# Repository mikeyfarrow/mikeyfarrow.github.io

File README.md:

# mikeyfarrow.github.io
Github pages homepage

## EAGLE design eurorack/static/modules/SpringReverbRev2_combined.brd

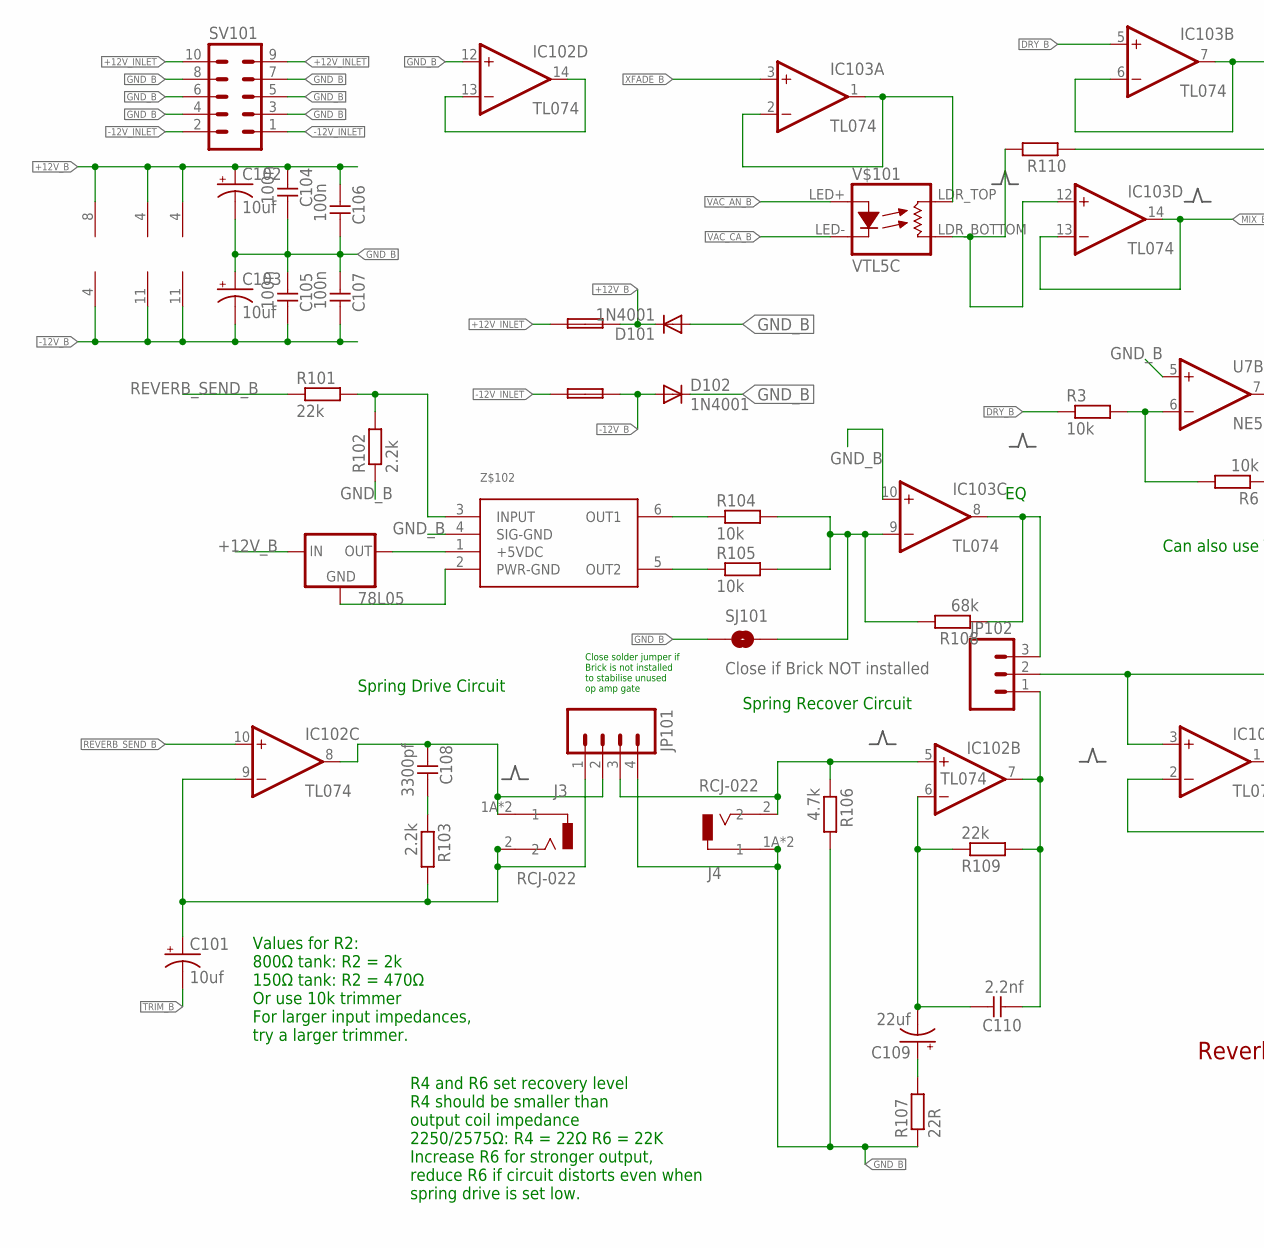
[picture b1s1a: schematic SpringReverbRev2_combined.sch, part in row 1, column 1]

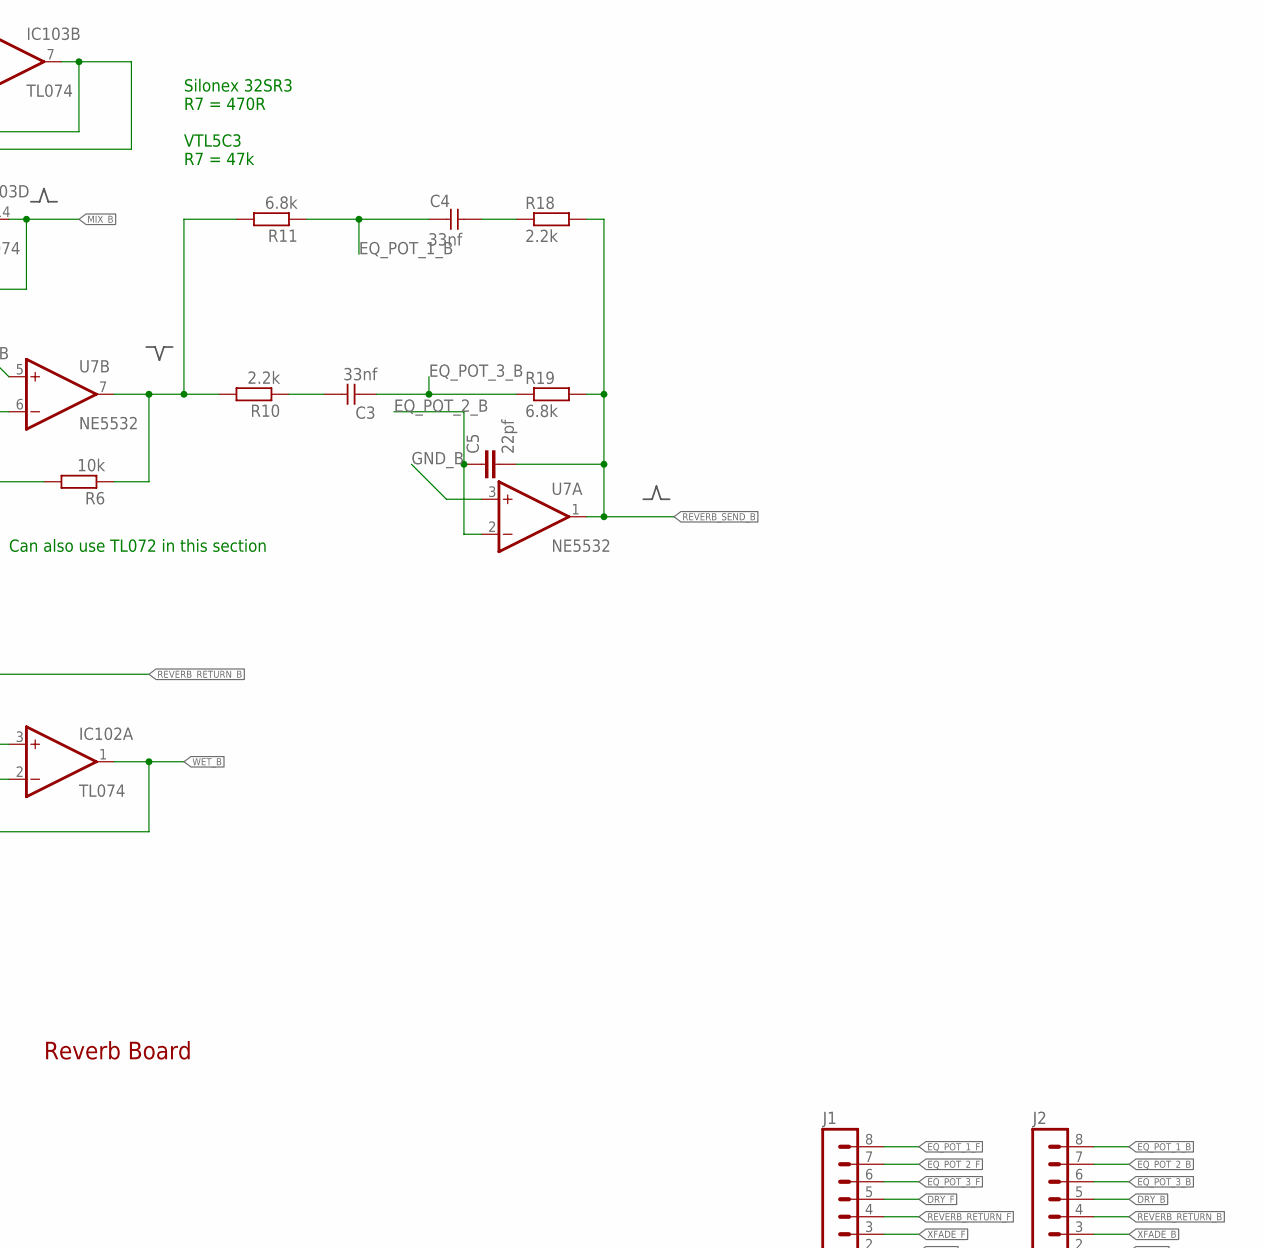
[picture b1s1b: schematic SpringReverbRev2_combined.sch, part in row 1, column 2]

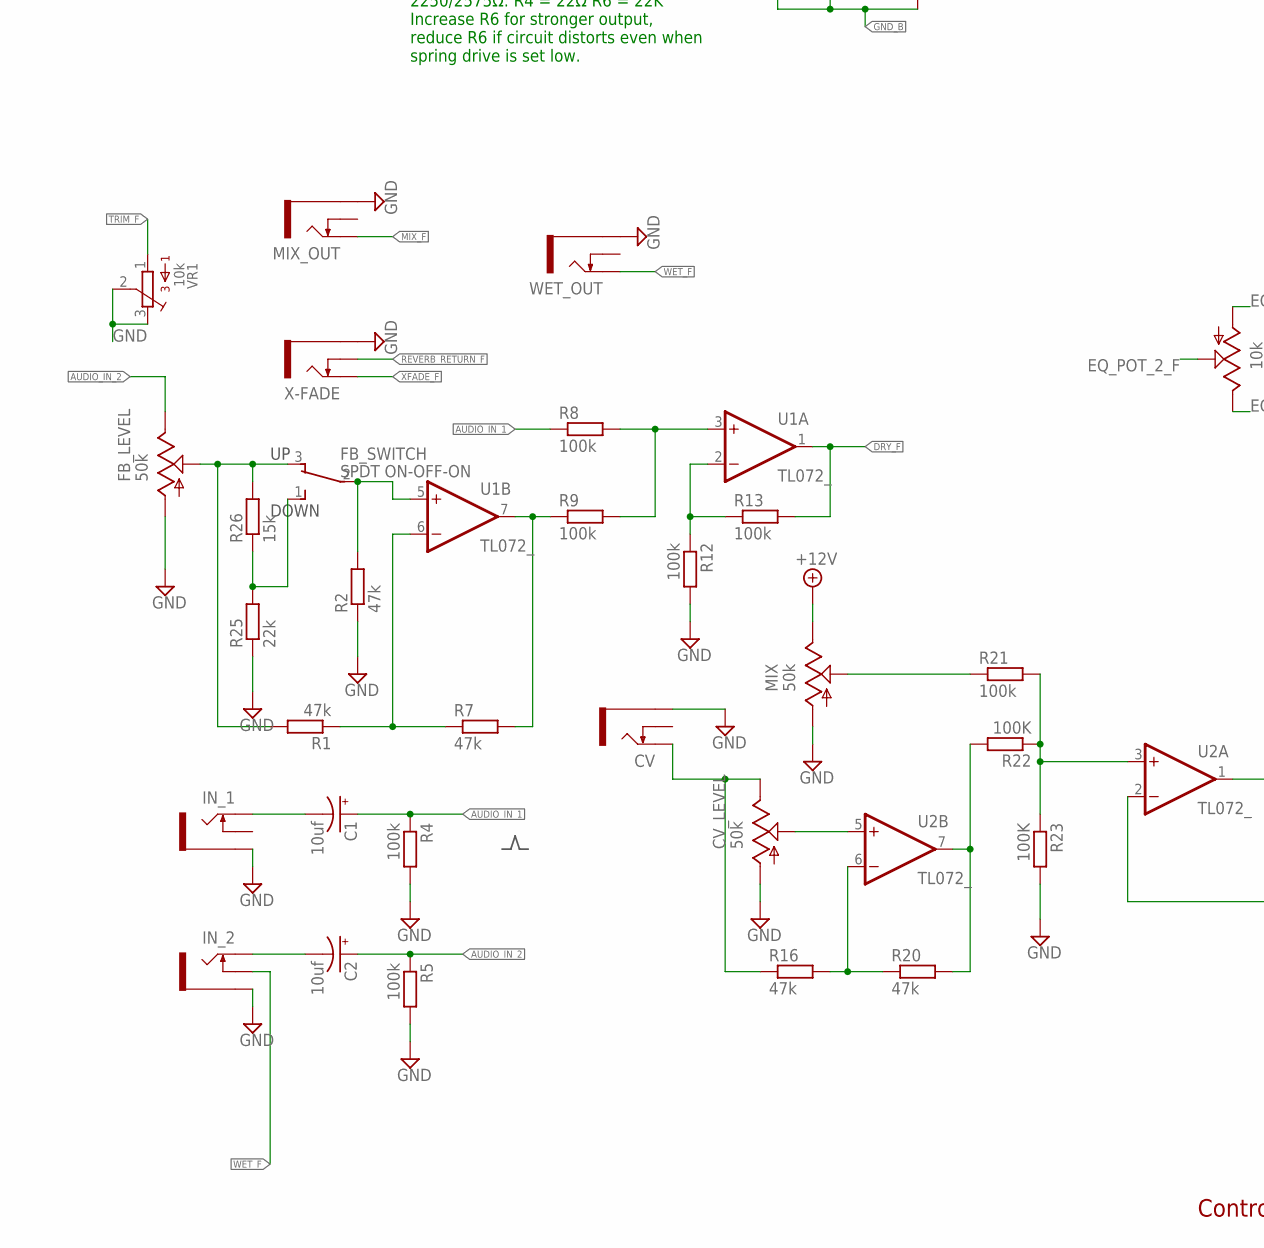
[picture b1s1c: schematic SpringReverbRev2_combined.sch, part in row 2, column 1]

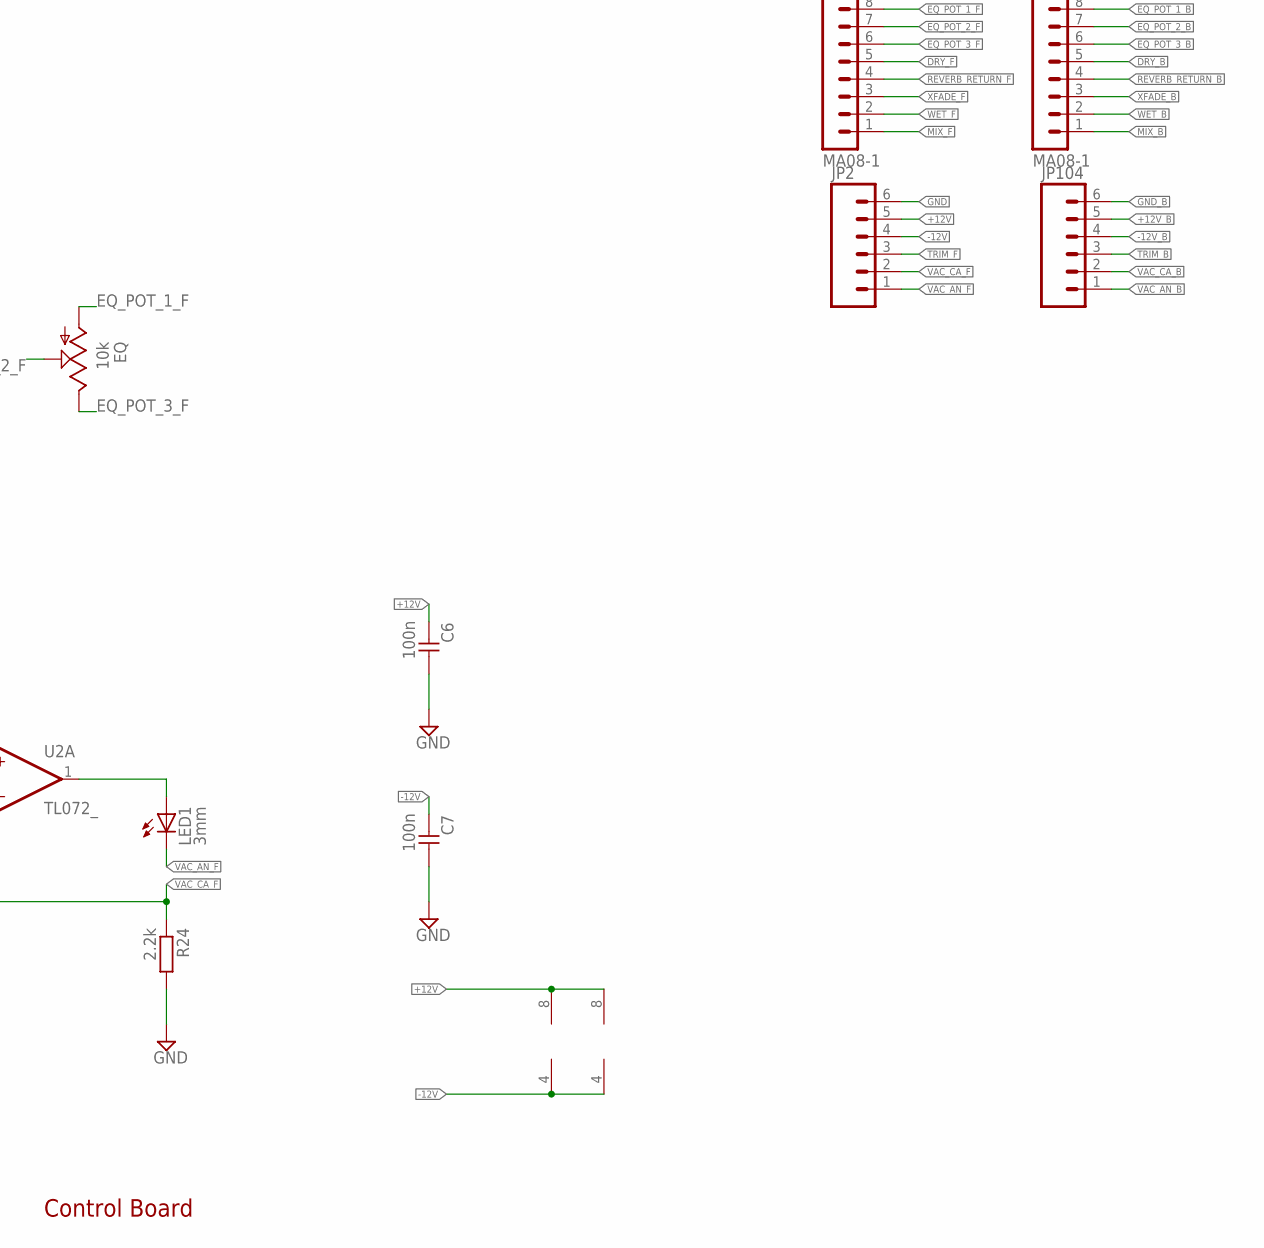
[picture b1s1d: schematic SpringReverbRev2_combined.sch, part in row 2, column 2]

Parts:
78L05: 78LXX
C1, C2: 10uf; 050_020
C3, C4: 33nf; C050-024X044
C5: 22pf; 050X030_025
C6, C7, C104, C105, C106, C107: 100n; C050-024X044
C101, C102, C103: 10uf; CPOL-RADIAL-10UF-25V
C108: 3300pf; C050-024X044
C109: 22uf; CPOL-RADIAL-10UF-25V
C110: 2.2nf; C050-024X044
CV: THONKICONNNEW; WQP-PJ301M-12_JACK
CV_LEVEL: 50k; EVUF
D101, D102: 1N4001; DO41-10
EQ: 10k; EVUF
F101, F102: FUSE; C050H075X075
FB_LEVEL: 50k; EVUF
FB_SWITCH: SPDT ON-OFF-ON; SPDT-VERTICAL-TOP-SUBMINI-MULTICOMP
IC102, IC103: TL074; DIL14
IN_1, IN_2: THONKICONNNEW; WQP-PJ301M-12_JACK
J1, J2: MA08-1
J3, J4: RCJ-022; CUI_RCJ-022
JP2, JP104: M06SIP; 1X06
JP101: M04POLAR; MOLEX-1X4
JP102: M03LOCK_NO_SILK; 1X03_LOCK_NO_SILK
LED1: 3mm; LED3MM
MIX: 50k; EVUF
MIX_OUT: THONKICONNNEW; WQP-PJ301M-12_JACK
R1, R2, R7, R16, R20: 47k; 7MM_RESISTOR
R3, R6, R104, R105: 10k; 7MM_RESISTOR
R4, R5, R8, R9, R12, R13, R21: 100k; 7MM_RESISTOR
R10, R18, R24, R102, R103: 2.2k; 7MM_RESISTOR
R11, R19: 6.8k; 7MM_RESISTOR
R22, R23: 100K; 7MM_RESISTOR
R25, R101, R109: 22k; 7MM_RESISTOR
R26: 15k; 7MM_RESISTOR
R106: 4.7k; 7MM_RESISTOR
R107: 22R; 7MM_RESISTOR
R108: 68k; 7MM_RESISTOR
R110: RESISTOR7MM; 7MM_RESISTOR
SJ101: Close if Brick NOT installed; SJ_2S-NOTRACE
SV101: 10_PIN_HEADER; MA05-2
U1, U2: TL072_; DIL08
U7: NE5532; DIL08
V$101: VTL5C; VACTROL_COMPACT
VR1: 10k; BOURNS_3362P_TRIMMER
WET_OUT: THONKICONNNEW; WQP-PJ301M-12_JACK
X-FADE: THONKICONNNEW; WQP-PJ301M-12_JACK
Z$102: BTDR-2H

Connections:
+12V: C6.2, JP2.5, MIX.3 (E), U1.8 (V+), U2.8 (V+)
+12V_B: 78L05.IN, C102.1 (+), C104.2, C106.2, D101.C, F101.1, IC102.4 (V+), IC103.4 (V+), JP104.5, U7.8 (V+)
+12V_INLET: F101.2, SV101.9, SV101.10
-12V: C7.2, JP2.4, U1.4 (V-), U2.4 (V-)
-12V_B: C103.2 (-), C105.1, C107.1, D102.A, F102.1, IC102.11 (V-), IC103.11 (V-), JP104.4, U7.4 (V-)
-12V_INLET: F102.2, SV101.1, SV101.2
AUDIO_IN_1: C1.+, R4.1, R8.1
AUDIO_IN_2: C2.+, FB_LEVEL.3 (E), R5.1
AUDIO_IN_BUF: IC103.6 (-IN), IC103.7 (OUT), R110.1
BRK: IC103.8 (OUT), JP102.3, R108.1
CV_F: R20.2, R22.2, U2.7 (OUT)
DRY_B: IC103.5 (+IN), J2.5, R3.1
DRY_F: J1.5, R13.2, U1.1 (OUT)
EQ_POT_1_B: C4.2, J2.8, R11.1
EQ_POT_1_F: EQ.1 (A), J1.8
EQ_POT_2_B: C5.1, J2.7, U7.2 (-IN)
EQ_POT_2_F: EQ.2 (S), J1.7
EQ_POT_3_B: C3.2, J2.6, R19.1
EQ_POT_3_F: EQ.3 (E), J1.6
GND: C6.1, C7.1, CV.P$3_SLEEVE (SLEEVE), CV_LEVEL.1 (A), FB_LEVEL.1 (A), IN_1.P$3_SLEEVE (SLEEVE), IN_2.P$3_SLEEVE (SLEEVE), JP2.6, MIX.1 (A), MIX_OUT.P$3_SLEEVE (SLEEVE), R2.1, R4.2, R5.2, R12.2, R23.2, R24.2, R25.1, VR1.2, VR1.3, WET_OUT.P$3_SLEEVE (SLEEVE), X-FADE.P$3_SLEEVE (SLEEVE)
GND_B: C102.2 (-), C103.1 (+), C104.1, C105.2, C106.1, C107.2, D101.A, D102.C, IC102.12 (+IN), IC103.10 (+IN), J4.1A (1), J4.1B (1), JP101.4, JP104.6, R102.1, R106.2, R107.1, SJ101.1, SV101.3, SV101.4, SV101.5, SV101.6, SV101.7, SV101.8, U7.3 (+IN), U7.5 (+IN), Z$102.4 (SIG-GND)
MIX_B: IC103.13 (-IN), IC103.14 (OUT), J2.1
MIX_F: J1.1, MIX_OUT.P$1_TIP (TIP)
unnamed: C1.-, IN_1.P$1_TIP (TIP)
unnamed: C2.-, IN_2.P$1_TIP (TIP)
unnamed: MIX.2 (S), R21.1
unnamed: FB_LEVEL.2 (S), FB_SWITCH.3, R1.2, R26.2
unnamed: R1.1, R7.1, U1.6 (-IN)
unnamed: R7.2, R9.1, U1.7 (OUT)
unnamed: R8.2, R9.2, U1.3 (+IN)
unnamed: R21.2, R22.1, R23.1, U2.3 (+IN)
unnamed: R12.1, R13.1, U1.2 (-IN)
unnamed: CV.P$1_TIP (TIP), CV_LEVEL.3 (E), R16.1
unnamed: LED1.A, U2.1 (OUT)
unnamed: FB_SWITCH.1, R25.2, R26.1
unnamed: C3.1, R10.1
unnamed: C109.1 (+), R107.2
unnamed: C109.2 (-), C110.1, IC102.6 (-IN), R109.1
unnamed: CV_LEVEL.2 (S), U2.5 (+IN)
unnamed: C4.1, R18.1
unnamed: R16.2, R20.1, U2.6 (-IN)
unnamed: R3.2, R6.2, U7.6 (-IN)
unnamed: C108.1, R103.1
unnamed: 78L05.OUT, Z$102.1 (+5VDC)
unnamed: R104.1, Z$102.6 (OUT1)
unnamed: R105.1, Z$102.5 (OUT2)
unnamed: IC103.9 (-IN), R104.2, R105.2, R108.2, SJ101.2
unnamed: R6.1, R10.2, R11.2, U7.7 (OUT)
unnamed: R101.2, R102.2, Z$102.3 (INPUT)
unnamed: 78L05.GND, Z$102.2 (PWR-GND)
unnamed: IC103.12 (+IN), R110.2, V$101.LDR_BOTTOM (RES2)
unnamed: IC102.13 (-IN), IC102.14 (OUT)
unnamed: FB_SWITCH.2, R2.2, U1.5 (+IN)
R+: IC102.5 (+IN), J4.2, JP101.3, R106.1
REVERB_RETURN_B: IC102.3 (+IN), J2.4, JP102.2
REVERB_RETURN_F: J1.4, X-FADE.P$2_SWITCH (SWITCH)
REVERB_SEND_B: C5.2, IC102.10 (+IN), R18.2, R19.2, R101.1, U7.1 (OUT)
S+: C101.1 (+), IC102.9 (-IN), J3.2, JP101.1, R103.2
S-: C108.2, IC102.8 (OUT), J3.1A (1), J3.1B (1), JP101.2
SPNG: C110.2, IC102.7 (OUT), JP102.1, R109.2
TRIM_B: C101.2 (-), JP104.3
TRIM_F: JP2.3, VR1.1
VAC_AN_B: JP104.1, V$101.LED+
VAC_AN_F: JP2.1, LED1.K (C)
VAC_CA_B: JP104.2, V$101.LED-
VAC_CA_F: JP2.2, R24.1, U2.2 (-IN)
WET_B: IC102.1 (OUT), IC102.2 (-IN), J2.2
WET_F: IN_2.P$2_SWITCH (SWITCH), J1.2, WET_OUT.P$1_TIP (TIP)
XFADE_B: IC103.3 (+IN), J2.3
XFADE_F: J1.3, X-FADE.P$1_TIP (TIP)
X_FADE_IN: IC103.1 (OUT), IC103.2 (-IN), V$101.LDR_TOP (RES1)

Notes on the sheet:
Control Board
Can also use TL072 in this section
Values for R2: 800Ω tank: R2 = 2k 150Ω tank: R2 = 470Ω Or use 10k trimmer For larger input impedances, try a larger trimmer.
Spring Drive Circuit
R4 and R6 set recovery level R4 should be smaller than output coil impedance 2250/2575Ω: R4 = 22Ω R6 = 22K Increase R6 for stronger output, reduce R6 if circuit distorts even when spring drive is set low.
Spring Recover Circuit
Reverb Board
Silonex 32SR3 R7 = 470R VTL5C3 R7 = 47k
Close solder jumper if Brick is not installed to stabilise unused op amp gate

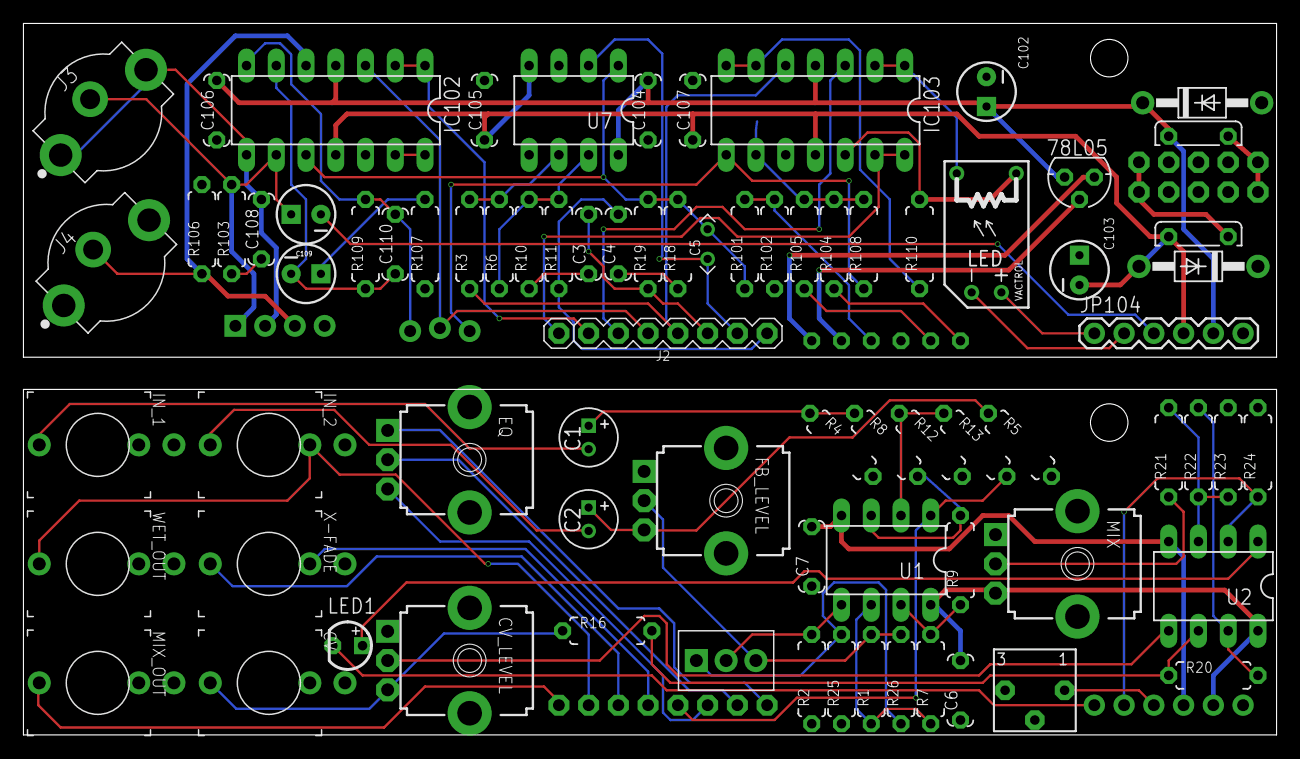
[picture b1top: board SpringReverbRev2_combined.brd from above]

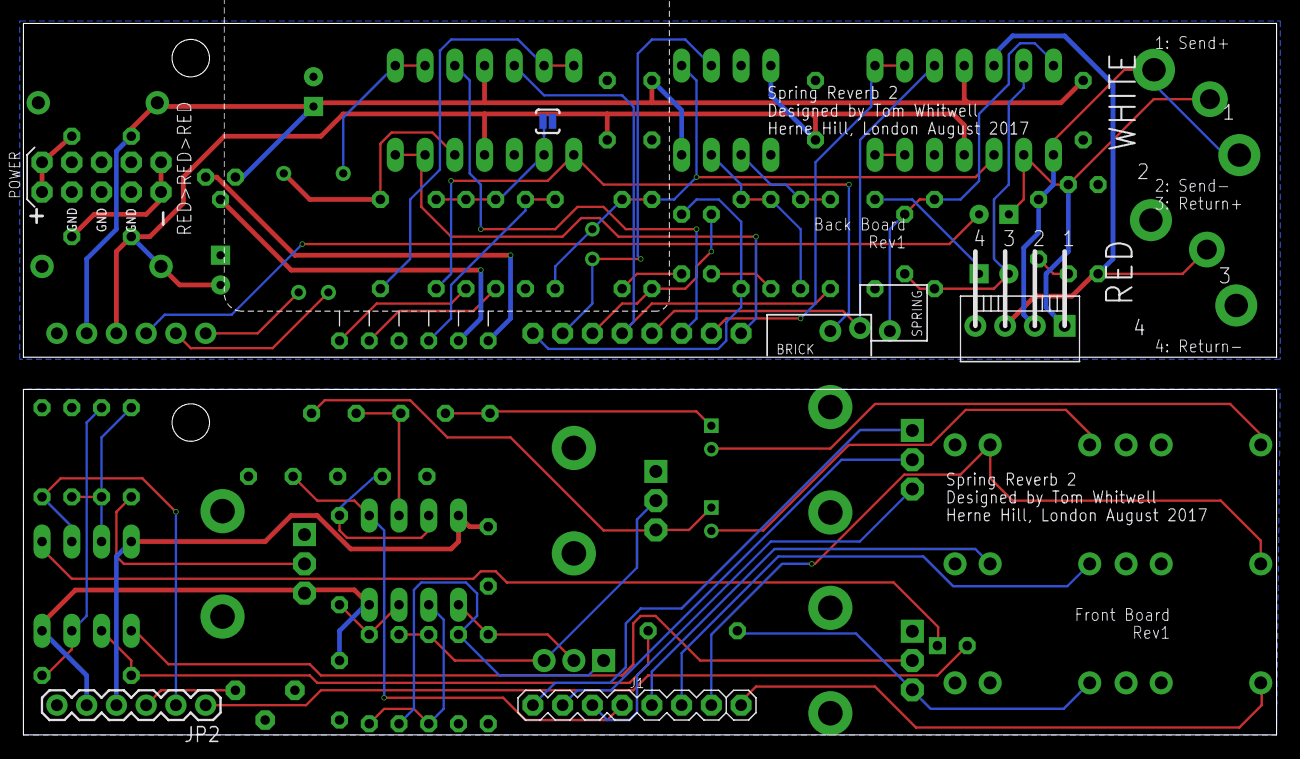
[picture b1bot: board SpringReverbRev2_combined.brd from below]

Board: 2 copper layers, 107.0 x 60.8 mm, 87 parts (7 on the bottom side), 71 nets.

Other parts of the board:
U$3, U$4: MOUNTING_HOLE

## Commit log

2024-03-21 home page placeholder
2024-03-21 adding pcb design files
2024-03-21 added index and 3d
2024-03-21 added links to references
2024-03-29 no iframes
2024-03-29 more links
2024-04-04 added tuning hw
2024-04-04 padding
2024-04-11 added ext in 3d
2024-04-12 update render
2024-04-12 renamed
2024-04-12 panel
2024-04-15 extin
2024-04-15 fix index
2024-04-15 remove iframe
2024-04-15 fix xhtml
2024-04-15 pics
2024-04-15 fix html
2024-04-15 Rename _config.yaml to _config.yml
2024-04-15 cleanup
2024-04-15 writeup
2024-04-15 image
2024-04-17 new index
2024-04-17 index
2024-04-17 images of pcb
2024-04-20 updated info
2024-04-20 add info
2024-04-20 formatting
2024-04-20 caveat
2024-04-30 updating images
2024-05-01 new render
2024-05-10 neural nets
2024-05-10 more nn
2024-05-14 hindi
2024-05-22 whale
2024-05-22 small
2024-05-24 whale wave
2024-05-29 embeds
2024-06-03 speech waves
    speech waves
2024-09-18 midifam
2024-09-19 trying jekyll
2025-04-08 added eurorack placeholder
2025-04-09 initial module descriptions

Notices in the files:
parts and their libraries:
SparkFun-Passives: Licensing: CC v3.0 Share-Alike You are welcome to use this library for commercial purposes.
